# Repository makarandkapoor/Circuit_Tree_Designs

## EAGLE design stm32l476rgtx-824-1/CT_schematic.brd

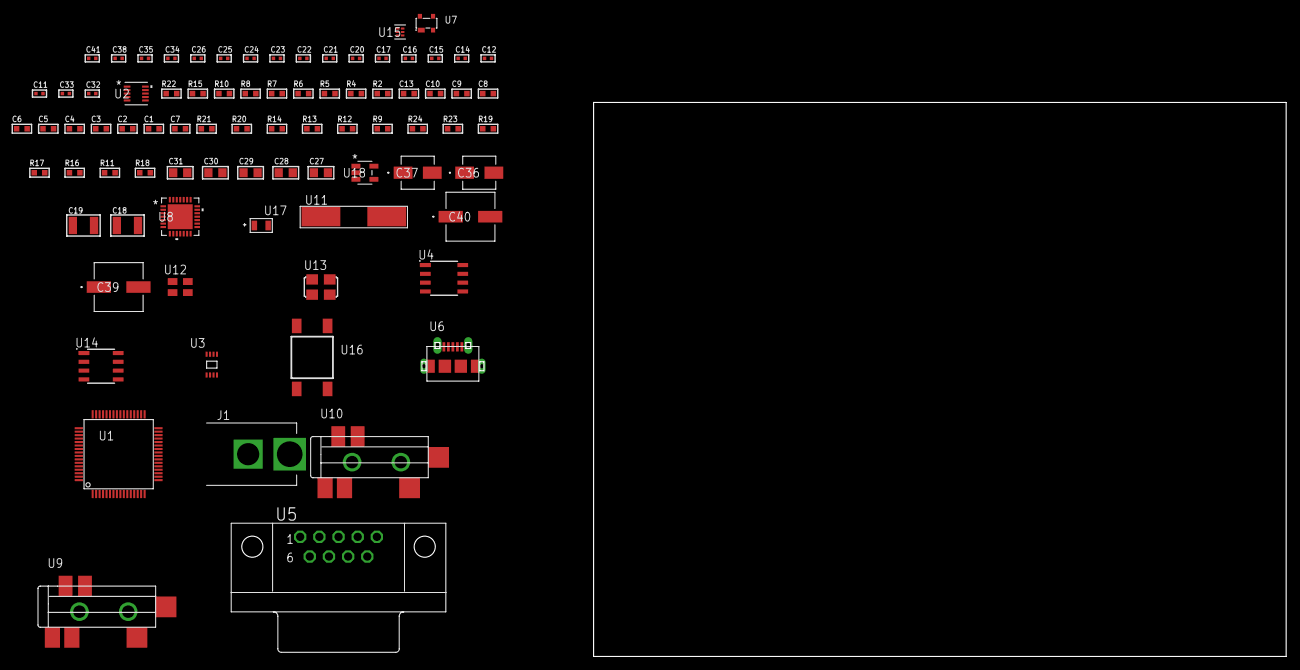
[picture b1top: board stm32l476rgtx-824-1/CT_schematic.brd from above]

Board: 2 copper layers, 124.8 x 80.0 mm, 82 parts (0 on the bottom side), 40 nets, no tracks yet.

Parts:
C1, C10, C13: 1e-06; C0603
C2, C3, C4, C5, C6, C8: 1e-07; C0603
C7: 4.7e-06; C0603
C9: 1e-08; C0603
C11, C12, C14, C15, C17, C22, C23, C24, C25, C26, C38: 1e-07; C0402
C16, C34, C35, C41: 1e-08; C0402
C18, C19: 2.2e-05; C1210
C20, C21: 1e-09; C0402
C27, C28, C29, C30, C31: 1e-05; C0805
C32, C33: 2.2e-11; C0402
C36: 1e-06; EXV-9B
C37: 2.2e-06; EXV-9B
C39, C40: 0.0001; EXV-9H
J1: PJ-037B; PJ-037B_PACKAGE
R2: 1000.0; R0603
R4: 4700.0; R0603
R5, R6, R7, R8: 2200.0; R0603
R9, R20, R21: 10000.0; R0603
R10: 120.0; R0603
R11: 470000.0; R0603
R12, R13, R14: 47000.0; R0603
R15: 680.0; R0603
R16, R17, R19: 100000.0; R0603
R18: 164658.62; R0603
R22: 9100.0; R0603
R23: 680000.0; R0603
R24: 120000.0; R0603
U1: STM32L476RGT6; LQFP64
U2: MAG3110FCR1; DFN-10
U3: 24AA02T-I/MNY; TDFN-8/6MM
U4: SN65HVD230D; SOIC-8
U5: 182-009-113R531; 182-009-MALE
U6: 47590-0001; MICRO_USB_AB
U7: prtr5v0u2ax; SOT143B
U8: WM8731CLSEFL; QFN-28
U9, U10: SJ-43515TS-SMT-TR
U11: ABLS-12.288MHZ-B4-T
U12: ASEK-32.768KHz-ECST; ASEK
U13: ASFL1-25MHZ-NCS; ASFL1
U14: LP2954AIMX/NOPB; LP2954
U15: TPS3895ADRYR; SON-6
U16: 4-1437565-2; SW_4-1437565-2
U17: Q65110A2395; LGM67K-G1J2-24-Z
U18: nc7sz125m5x; NC7SZ125M5X

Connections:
CLK_CRYSTAL_U8_1: C32.1, U8.1, U11.1
CLK_CRYSTAL_U8_2: C33.1, U8.2, U11.2
CLK_U1_3: U1.3, U12.3
CLK_U1_5: U1.5, U13.3
GND: C1.2, C2.2, C3.2, C4.2, C5.2, C6.2, C7.2, C8.2, C9.2, C10.2, C11.2, C12.2, C13.2, C14.2, C15.2, C16.2, C17.2, C21.2, C22.2, C23.2, C24.2, C25.2, C26.2, C27.2, C28.2, C29.2, C30.2, C31.2, C32.2, C33.2, C34.2, C35.2, C36.2, C37.2, C38.2, C39.2, C40.2, C41.2, J1.2, R2.2, R9.2, R11.2, R12.2, R13.2, R14.2, R19.2, R22.2, R24.2, U1.12, U1.18, U1.31, U1.47, U1.63, U2.5, U2.10, U3.4, U3.7, U4.2, U5.5, U6.5, U6.6, U6.7, U6.8, U6.9, U7.1, U8.4, U8.15, U8.19, U8.25, U8.26, U8.29, U9.1, U10.1, U12.2, U13.2, U14.4, U15.2, U17.C, U18.1, U18.3
NET_U1_7: R4.1, U1.7, U18.4
NET_U1_29: R7.1, U1.29, U3.6
NET_U1_30: R8.1, U1.30, U3.5
NET_U1_56: U16.3, U16.4
NET_U1_58: R5.1, U1.58, U2.7
NET_U1_59: R6.1, U1.59, U2.6
NET_U1_60: R9.1, U1.60
NET_U2_1: C11.1, U2.1
NET_U2_4: C14.1, U2.4
NET_U4_6: R10.2, U4.6
NET_U4_8: R11.1, U4.8
NET_U5_2: R10.2, U4.6, U5.2
NET_U5_3: R10.1, U4.7, U5.3
NET_U8_20: C26.1, C31.1, U8.20
NET_U9_2: C19.1, R13.1, U9.2
NET_U9_5: C18.1, R12.1, U9.5
NET_U10_5: C20.1, C21.1, R14.1, R15.1, U10.5
NET_U14_3: R17.1, U14.3
NET_U14_5: R16.1, U14.5
NET_U14_7: R18.2, R19.1, U14.7
NET_U15_1: R21.1, R22.1, U15.1
NET_U15_3: R23.2, R24.1, U15.3
NET_U15_4: R20.1, U15.4, U18.2
NET_U16_1: R2.1, U16.1, U16.2
PROC_CAN1_RX: U1.61, U4.4
PROC_CAN1_TX: U1.62, U4.1
PROC_SAI1_FS_B: U1.20, U8.9, U8.11
PROC_SAI1_SCK_B: U1.55, U8.7
PROC_SAI1_SD_B: U1.57, U8.8
PROC_USB_OTG_FS_DM: U1.44, U6.2, U7.3
PROC_USB_OTG_FS_DP: U1.45, U6.3, U7.2
PROC_USB_OTG_FS_ID: U1.43, U6.4
PROC_USB_OTG_FS_VBUS: U1.42, U6.1, U7.4
VCC_S1_8V1: C36.1, C39.1, C40.1, J1.1, R17.2, U14.8
VCC_TIER1_3V3: C1.1, C2.1, C3.1, C4.1, C5.1, C6.1, C7.1, C8.1, C9.1, C10.1, C12.1, C13.1, C15.1, C16.1, C17.1, C22.1, C23.1, C24.1, C25.1, C27.1, C28.1, C29.1, C30.1, C34.1, C35.1, C37.1, C38.1, C41.1, R4.2, R5.2, R6.2, R7.2, R8.2, R16.2, R18.1, R20.2, R21.2, R23.1, U1.1, U1.13, U1.19, U1.32, U1.48, U1.64, U2.2, U2.8, U3.8, U4.3, U8.3, U8.5, U8.12, U8.18, U12.4, U13.4, U14.1, U15.6, U18.5

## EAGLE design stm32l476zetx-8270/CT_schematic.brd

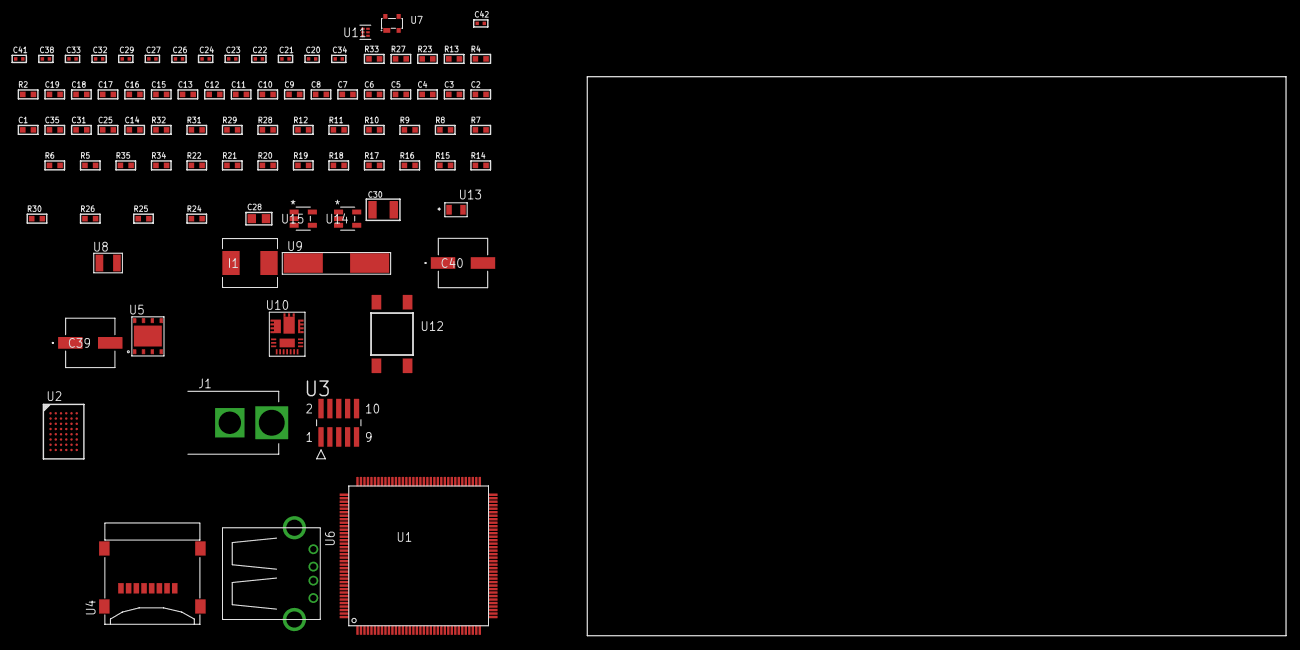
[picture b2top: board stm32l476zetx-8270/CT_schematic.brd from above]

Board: 2 copper layers, 100.0 x 80.0 mm, 90 parts (0 on the bottom side), 83 nets, no tracks yet.

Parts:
C1, C19: 1e-06; C0603
C2, C3, C4, C5, C6, C7, C8, C9, C10, C11, C12, C13, C15, C16, C17: 1e-07; C0603
C14: 4.7e-06; C0603
C18: 1e-08; C0603
C20, C21, C22, C23: 1e-11; C0402
C24, C26, C27, C29, C32, C33, C38: 1e-07; C0402
C25, C31: 2.2e-06; C0603
C28: 1e-05; C0805
C30: 0.0001; C1210
C34: 8.2e-09; C0402
C35: 2.7e-07; C0603
C39, C40: 0.0001; EXV-9H
C41, C42: 1e-08; C0402
I1: 6.8e-07; IND25X25CZ
J1: PJ-037B; PJ-037B_PACKAGE
R2: 1000.0; R0603
R4: 4700.0; R0603
R5, R6, R7, R8, R9, R10, R11, R12, R31, R32: 10000.0; R0603
R13: 5.0; R0603
R14, R15, R16, R17, R18, R19, R20, R21, R22: 100000.0; R0603
R23: 0.1; R0603
R24: 4030.2416170974; R0603
R25: 719.68600305311; R0603
R26: 64.583209876543; R0603
R27: 130.0; R0603
R28: 39000.0; R0603
R29: 49900.0; R0603
R30: 5359.1232876712; R0603
R33: 9100.0; R0603
R34: 680000.0; R0603
R35: 120000.0; R0603
U1: STM32L476ZET6; LQFP144
U2: CY62147GE30-45BVXI; VFBGA48
U3: FTSH-105-01-L-DV-K; SAMTEC_FTSH-105-01-L-DV-K
U4: 0472192001; MOLEX_47219-2001
U5: SST26VF016B-104I/MF; WFDN-8
U6: 61400416021; USB-A-H
U7: prtr5v0u2ax; SOT143B
U8: ABS07-32.768KHZ-7-T
U9: ABLS-25.000MHZ-B2F-T
U10: IR3899MTR1PBF
U11: TPS3895ADRYR; SON-6
U12: 4-1437565-2; SW_4-1437565-2
U13: Q65110A2395; LGM67K-G1J2-24-Z
U14, U15: nc7sz125m5x; NC7SZ125M5X

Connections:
CLK_CRYSTAL_U1_8: C20.1, U1.8, U8.1
CLK_CRYSTAL_U1_9: C21.1, U1.9, U8.2
CLK_CRYSTAL_U1_23: C22.1, U1.23, U9.1
CLK_CRYSTAL_U1_24: C23.1, U1.24, U9.2
GND: C1.2, C2.2, C3.2, C4.2, C5.2, C6.2, C7.2, C8.2, C9.2, C10.2, C11.2, C12.2, C13.2, C14.2, C15.2, C16.2, C17.2, C18.2, C19.2, C20.2, C21.2, C22.2, C23.2, C24.2, C25.2, C26.2, C27.2, C28.2, C29.2, C31.2, C32.2, C33.2, C38.2, C39.2, C40.2, C41.2, C42.2, J1.2, R2.2, R5.2, R12.2, R13.2, R23.1, R23.2, R25.2, R28.2, R30.2, R33.2, R35.2, U1.16, U1.30, U1.31, U1.38, U1.51, U1.61, U1.71, U1.83, U1.94, U1.107, U1.120, U1.130, U1.143, U2.D1, U2.E6, U3.3, U3.5, U4.6, U4.G1, U4.G2, U4.G3, U4.G4, U5.4, U5.9, U6.4, U6.5, U6.6, U7.1, U10.4, U10.11, U10.17, U11.2, U13.C, U14.2, U14.3, U15.1, U15.3
NET_U1_25: R4.1, U1.25, U15.4
NET_U1_138: R5.1, U1.138
NET_U1_142: U12.3, U12.4
NET_U3_9: R13.1, U3.9
NET_U10_1: C34.1, R24.1, R25.1, R26.1, R27.1, U10.1, U10.8
NET_U10_2: C33.1, U10.2
NET_U10_3: C34.2, C35.1, C35.2, U10.3
NET_U10_5: R28.1, U10.5
NET_U10_10: C31.1, U10.10
NET_U10_12: C30.1, I1.1, U10.12
NET_U10_14: C30.2, U10.14
NET_U10_15: R29.1, R30.1, U10.15
NET_U10_ATNET_3: I1.2, R24.2
NET_U10_ATNET_4: C35.2, R26.2
NET_U11_1: R32.1, R33.1, U11.1
NET_U11_3: R34.2, R35.1, U11.3
NET_U11_4: R31.1, U11.4, U14.4, U15.2
NET_U12_1: R2.1, U12.1, U12.2
PROC_FMC_A0: U1.10, U2.A3
PROC_FMC_A1: U1.11, U2.A4
PROC_FMC_A2: U1.12, U2.A5
PROC_FMC_A3: U1.13, U2.B3
PROC_FMC_A4: U1.14, U2.B4
PROC_FMC_A5: U1.15, U2.C3
PROC_FMC_A6: U1.50, U2.C4
PROC_FMC_A7: U1.53, U2.D4
PROC_FMC_A8: U1.54, U2.H2
PROC_FMC_A9: U1.55, U2.H3
PROC_FMC_A10: U1.56, U2.H4
PROC_FMC_A11: U1.57, U2.H5
PROC_FMC_A12: U1.87, U2.G3
PROC_FMC_A13: U1.88, U2.G4
PROC_FMC_A14: U1.89, U2.F3
PROC_FMC_A15: U1.90, U2.F4
PROC_FMC_A16: U1.80, U2.E4
PROC_FMC_A17: U1.81, U2.D3
PROC_FMC_D0: U1.85, U2.B6
PROC_FMC_D1: U1.86, U2.C5
PROC_FMC_D2: U1.114, U2.C6
PROC_FMC_D3: U1.115, U2.D5
PROC_FMC_D4: U1.58, U2.E5
PROC_FMC_D5: U1.59, U2.F5
PROC_FMC_D6: U1.60, U2.F6
PROC_FMC_D7: U1.63, U2.G6
PROC_FMC_D8: U1.64, U2.B1
PROC_FMC_D9: U1.65, U2.C1
PROC_FMC_D10: U1.66, U2.C2
PROC_FMC_D11: U1.67, U2.D2
PROC_FMC_D12: U1.68, U2.E2
PROC_FMC_D13: U1.77, U2.F2
PROC_FMC_D14: U1.78, U2.F1
PROC_FMC_D15: U1.79, U2.G1
PROC_FMC_NBL0: U1.141, U2.A1
PROC_FMC_NE2: R7.1, U1.124, U2.B5
PROC_FMC_NOE: R6.1, U1.118, U2.A2
PROC_FMC_NWE: R8.1, U1.119, U2.G5
PROC_QUADSPI_BK1_IO0: U1.47, U5.5
PROC_QUADSPI_BK1_IO1: U1.46, U5.2
PROC_QUADSPI_BK1_IO2: R21.1, U1.43, U5.3
PROC_QUADSPI_BK1_IO3: R22.1, U1.42, U5.7
PROC_QUADSPI_CLK: U1.69, U5.6
PROC_QUADSPI_NCS: R20.1, U1.70, U5.1
PROC_SDMMC1_CK: R15.1, U1.113, U4.5
PROC_SDMMC1_CMD: R14.1, U1.116, U4.3
PROC_SDMMC1_D0: R16.1, U1.98, U4.7
PROC_SDMMC1_D1: R17.1, U1.99, U4.8
PROC_SDMMC1_D2: R18.1, U1.111, U4.1
PROC_SDMMC1_D3: R19.1, U1.112, U4.2
PROC_SYS_JTCK_SWCLK: R12.1, U1.109, U3.4
PROC_SYS_JTDI: R10.1, U1.110, U3.8
PROC_SYS_JTDO_SWO: U1.133, U3.6
PROC_SYS_JTMS_SWDIO: R11.1, U1.105, U3.2
PROC_USB_OTG_FS_DM: U1.103, U6.2, U7.3
PROC_USB_OTG_FS_DP: U1.104, U6.3, U7.2
PROC_USB_OTG_FS_VBUS: U1.101, U6.1, U7.4
RST_OUT_U3_JTAG_RST_B: R9.1, U3.10, U14.1
VCC_S1_16V2: C32.1, C39.1, C40.1, J1.1, R29.2, U10.9
VCC_TIER1_3V3: C1.1, C2.1, C3.1, C4.1, C5.1, C6.1, C7.1, C8.1, C9.1, C10.1, C11.1, C12.1, C13.1, C14.1, C15.1, C16.1, C17.1, C18.1, C19.1, C24.1, C25.1, C26.1, C27.1, C28.1, C29.1, C38.1, C41.1, C42.1, I1.2, R4.2, R6.2, R7.2, R8.2, R9.2, R10.2, R11.2, R14.2, R15.2, R16.2, R17.2, R18.2, R19.2, R20.2, R21.2, R22.2, R24.2, R31.2, R32.2, R34.1, U1.6, U1.17, U1.32, U1.33, U1.39, U1.52, U1.62, U1.72, U1.84, U1.95, U1.106, U1.108, U1.121, U1.131, U1.144, U2.D6, U2.E1, U3.1, U4.4, U5.8, U11.6, U14.5, U15.5

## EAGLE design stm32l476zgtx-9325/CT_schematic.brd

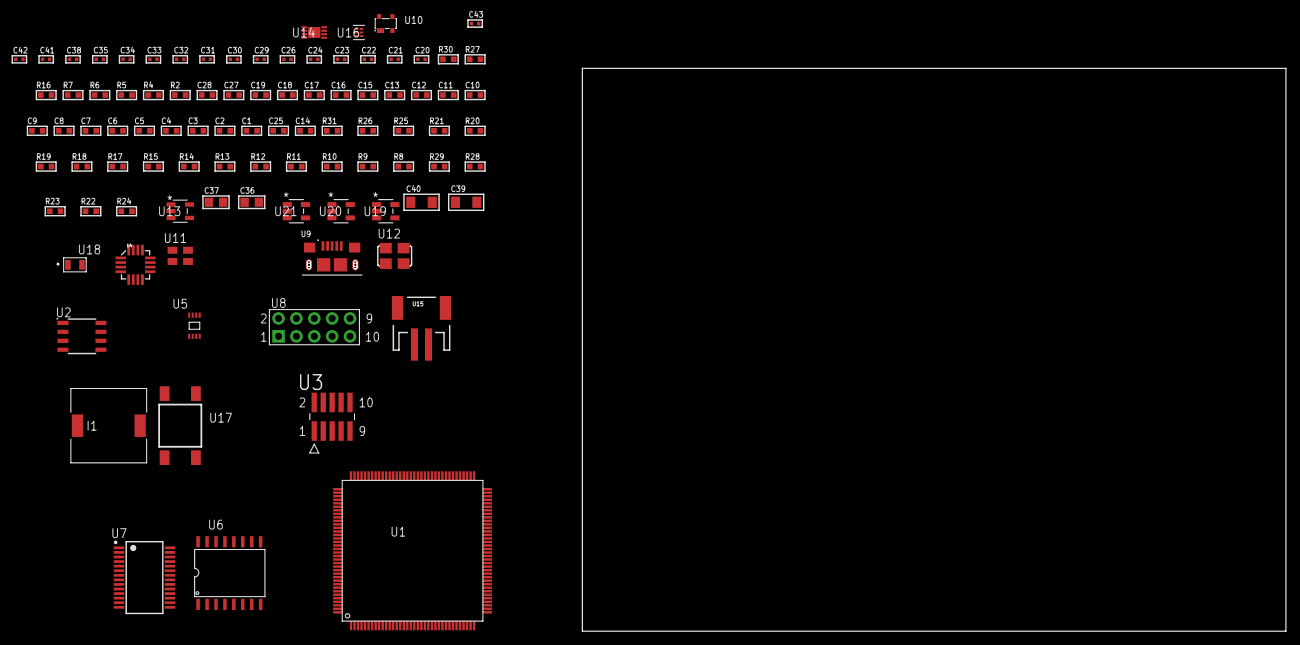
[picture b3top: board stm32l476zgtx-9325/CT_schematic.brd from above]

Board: 2 copper layers, 94 parts (0 on the bottom side), 61 nets, no tracks yet.

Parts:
C1, C19, C27, C28: 1e-06; C0603
C2, C3, C4, C5, C6, C7, C8, C9, C10, C11, C12, C13, C15, C16, C17: 1e-07; C0603
C14: 4.7e-06; C0603
C18: 1e-08; C0603
C20, C22, C23, C24, C26, C34, C35, C41, C42, C43: 1e-08; C0402
C21, C29, C30, C31, C32, C33, C38: 1e-07; C0402
C25: 4.7e-07; C0603
C36, C37: 1e-05; C0805
C39, C40: 1e-05; C1206
I1: 2.5e-06; DR1040
R2: 1000.0; R0603
R4, R5: 4700.0; R0603
R6, R7: 2200.0; R0603
R8, R9, R10, R11, R12, R13, R14, R15, R17, R18, R19, R20, R21, R25, R26, R31: 10000.0; R0603
R16: 5.0; R0603
R22: 100000.0; R0603
R23: 220000.0; R0603
R24: 1000000.0; R0603
R27: 9100.0; R0603
R28: 680000.0; R0603
R29: 120000.0; R0603
R30: 2000.0; R0603
U1: STM32L476ZGT6; LQFP144
U2: AT25020B-SSHL-T; SOIC-8
U3: FTSH-105-01-L-DV-K; SAMTEC_FTSH-105-01-L-DV-K
U4: l3g4200d; LGA-16
U5: 24AA16-I/MC; TDFN-8/6MM
U6: S25FL128SDSMFI000
U7: ST3241EBPR; SSOP-28
U8: HTSS-105-01-G-D
U9: 10118193-0001LF; FCI_10118193-0001LF
U10: prtr5v0u2ax; SOT143B
U11: ASEK-32.768KHz-ECST; ASEK
U12: ASFL1-25MHZ-NCS; ASFL1
U13: ltc3406es5; TSOT-23-5
U14: MCP73831T-2ACI/MC; DFN8_2X3MC
U15: S2B-PH-SM4-TB(LF)(SN); JST-2-SMD
U16: TPS3895ADRYR; SON-6
U17: 4-1437565-2; SW_4-1437565-2
U18: Q65110A2395; LGM67K-G1J2-24-Z
U19, U20, U21: nc7sz125m5x; NC7SZ125M5X

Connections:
CLK_U1_8: U1.8, U11.3
CLK_U1_23: U1.23, U12.3
GND: C1.2, C2.2, C3.2, C4.2, C5.2, C6.2, C7.2, C8.2, C9.2, C10.2, C11.2, C12.2, C13.2, C14.2, C15.2, C16.2, C17.2, C18.2, C19.2, C20.2, C21.2, C22.2, C23.2, C24.2, C26.2, C27.2, C28.2, C29.2, C32.2, C33.2, C34.2, C35.2, C36.2, C37.1, C37.2, C38.2, C39.2, C40.2, C41.2, C42.2, C43.2, R2.2, R8.2, R15.2, R16.2, R17.1, R17.2, R23.2, R27.2, R29.2, R30.2, U1.16, U1.30, U1.31, U1.38, U1.51, U1.61, U1.71, U1.83, U1.94, U1.107, U1.120, U1.130, U1.143, U2.4, U3.3, U3.5, U4.8, U4.9, U4.10, U4.11, U4.12, U4.13, U5.4, U5.7, U6.10, U7.23, U7.25, U8.9, U9.5, U9.6, U9.7, U9.8, U9.9, U10.1, U11.2, U12.2, U13.2, U14.6, U14.9, U15.2, U16.2, U18.C, U19.2, U19.3, U20.1, U20.3, U21.1, U21.3
INPUT_USBPOWER_5V: C39.1, R31.2, U9.1, U10.4, U14.1, U14.2
NET_U1_25: R5.1, U1.25, U21.4
NET_U1_128: R7.1, U1.128, U5.5
NET_U1_129: R6.1, U1.129, U5.6
NET_U1_138: R8.1, U1.138
NET_U1_142: U17.3, U17.4
NET_U2_3: R9.1, U2.3
NET_U2_7: R11.1, U2.7
NET_U3_9: R16.1, U3.9
NET_U4_14: C24.1, C25.1, U4.14
NET_U6_3: R4.1, U6.3, U20.4
NET_U7_1: C31.1, U7.1
NET_U7_2: C31.2, U7.2
NET_U7_3: C33.1, U7.3
NET_U7_22: R22.1, U7.22
NET_U7_24: C30.2, U7.24
NET_U7_27: C32.1, U7.27
NET_U7_28: C30.1, U7.28
NET_U8_3: U7.4, U8.3
NET_U8_4: U7.5, U8.4
NET_U8_5: U7.9, U8.5
NET_U8_6: U7.10, U8.6
NET_U13_3: I1.1, U13.3
NET_U13_5: R23.1, R24.1, U13.5
NET_U13_ATNET_3: I1.2, R24.2
NET_U14_5: R31.1, U14.5
NET_U14_8: R30.1, U14.8
NET_U16_1: R26.1, R27.1, U16.1
NET_U16_3: R28.2, R29.1, U16.3
NET_U16_4: R25.1, U16.4, U19.4, U20.2, U21.2
NET_U17_1: R2.1, U17.1, U17.2
PROC_LPUART1_CTS: U1.74, U7.13
PROC_LPUART1_RTS: U1.73, U7.18
PROC_LPUART1_RX: U1.26, U7.19
PROC_LPUART1_TX: U1.27, U7.14
PROC_QUADSPI_BK1_IO0: U1.47, U6.15
PROC_QUADSPI_BK1_IO1: U1.46, U6.8
PROC_QUADSPI_BK1_IO2: R20.1, U1.43, U6.9
PROC_QUADSPI_BK1_IO3: R21.1, U1.42, U6.1
PROC_QUADSPI_CLK: U1.63, U6.16
PROC_QUADSPI_NCS: R19.1, U1.64, U6.7
PROC_SPI1_MISO: U1.67, U4.4
PROC_SPI1_MOSI: U1.68, U4.3
PROC_SPI1_NSS: R18.1, U1.40, U4.5
PROC_SPI1_SCK: U1.41, U4.2
PROC_SPI2_MISO: U1.28, U2.2
PROC_SPI2_MOSI: U1.29, U2.5
PROC_SPI2_NSS: R10.1, U1.114, U2.1
PROC_SPI2_SCK: U1.69, U2.6
PROC_SYS_JTCK_SWCLK: R15.1, U1.109, U3.4
PROC_SYS_JTDI: R13.1, U1.110, U3.8
PROC_SYS_JTDO_SWO: U1.133, U3.6
PROC_SYS_JTMS_SWDIO: R14.1, U1.105, U3.2
PROC_USB_OTG_FS_DM: U9.2, U10.3
PROC_USB_OTG_FS_DP: U9.3, U10.2
RST_OUT_U3_JTAG_RST_B: R12.1, U3.10, U19.1
VCC_S1_3V7: C36.1, C40.1, U13.4, U14.3, U14.4, U15.1
VCC_TIER1_3V3: C1.1, C2.1, C3.1, C4.1, C5.1, C6.1, C7.1, C8.1, C9.1, C10.1, C11.1, C12.1, C13.1, C14.1, C15.1, C16.1, C17.1, C18.1, C19.1, C20.1, C21.1, C22.1, C23.1, C26.1, C27.1, C28.1, C29.1, C34.1, C35.1, C37.2, C38.1, C41.1, C42.1, C43.1, I1.2, R4.2, R5.2, R6.2, R7.2, R9.2, R10.2, R11.2, R12.2, R13.2, R14.2, R18.2, R19.2, R20.2, R21.2, R22.2, R24.2, R25.2, R26.2, R28.1, U1.6, U1.17, U1.32, U1.33, U1.39, U1.52, U1.62, U1.72, U1.84, U1.95, U1.106, U1.108, U1.121, U1.131, U1.144, U2.8, U3.1, U4.1, U4.15, U4.16, U5.8, U6.2, U6.14, U7.26, U11.4, U12.4, U16.6, U19.5, U20.5, U21.5

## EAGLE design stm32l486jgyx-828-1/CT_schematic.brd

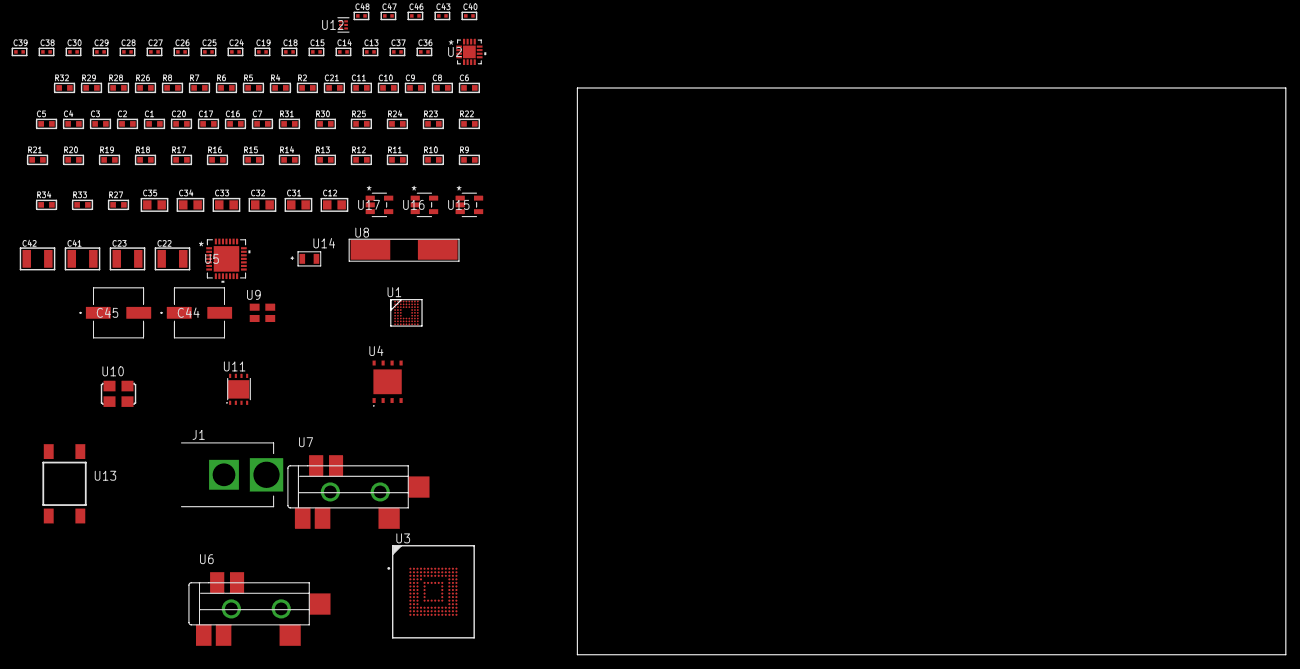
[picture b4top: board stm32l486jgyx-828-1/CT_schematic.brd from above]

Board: 2 copper layers, 126.3 x 80.0 mm, 98 parts (0 on the bottom side), 47 nets, no tracks yet.

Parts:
C1, C11, C21: 1e-06; C0603
C2, C3, C4, C5, C6, C8, C9: 1e-07; C0603
C7: 4.7e-06; C0603
C10: 1e-08; C0603
C12: 4.7e-06; C0805
C13, C14, C15, C18, C19, C26, C27, C28, C29, C30, C43: 1e-07; C0402
C16, C17, C20: 2.2e-06; C0603
C22, C23: 2.2e-05; C1210
C24, C25: 1e-09; C0402
C31, C32, C33, C34, C35: 1e-05; C0805
C36, C37: 2.2e-11; C0402
C38, C39, C40, C46, C47, C48: 1e-08; C0402
C41, C42: 1e-05; C1210
C44, C45: 0.0001; EXV-9H
J1: PJ-037B; PJ-037B_PACKAGE
R2, R29: 1000.0; R0603
R4, R5, R6: 4700.0; R0603
R7, R8: 2200.0; R0603
R9, R10, R21, R22, R30, R31: 10000.0; R0603
R11, R12, R13, R14, R15, R16, R17, R18, R19, R20: 34000.0; R0603
R23, R24, R25: 47000.0; R0603
R26: 680.0; R0603
R27: 100000.0; R0603
R28: 2231.0; R0603
R32: 9100.0; R0603
R33: 680000.0; R0603
R34: 120000.0; R0603
U1: STM32L486JGY6; WLCSP72
U2: MMA8451QT; QFN-16
U3: mtfc4gmcdm; TFBGA-153
U4: MX25R6435FZAIH0; WSON-8-PAD
U5: WM8731CLSEFL; QFN-28
U6, U7: SJ-43515TS-SMT-TR
U8: ABLS-12.288MHZ-B4-T
U9: ASEK-32.768KHz-ECST; ASEK
U10: ASFL1-25MHZ-NCS; ASFL1
U11: LP3878SDX-ADJ/NOPB; WSON-8
U12: TPS3895ADRYR; SON-6
U13: 4-1437565-2; SW_4-1437565-2
U14: Q65110A2395; LGM67K-G1J2-24-Z
U15, U16, U17: nc7sz125m5x; NC7SZ125M5X

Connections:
CLK_CRYSTAL_U5_1: C36.1, U5.1, U8.1
CLK_CRYSTAL_U5_2: C37.1, U5.2, U8.2
CLK_U1_C9: U1.C9, U9.3
CLK_U1_D9: U1.D9, U10.3
GND: C1.2, C2.2, C3.2, C4.2, C5.2, C6.2, C7.2, C8.2, C9.2, C10.2, C11.2, C12.2, C13.2, C14.2, C15.2, C16.2, C17.2, C18.2, C19.2, C20.2, C21.2, C25.2, C26.2, C27.2, C28.2, C29.2, C30.2, C31.2, C32.2, C33.2, C34.2, C35.2, C36.2, C37.2, C38.2, C39.2, C40.2, C41.2, C42.2, C43.2, C44.2, C45.2, C46.2, C47.2, C48.2, J1.2, R2.2, R9.2, R23.2, R24.2, R25.2, R29.2, R32.2, R34.2, U1.A8, U1.B1, U1.G9, U1.J2, U1.J9, U2.5, U2.10, U2.12, U2.17, U3.C4, U3.E7, U3.G5, U3.H10, U3.K8, U3.N2, U3.N5, U3.P4, U3.P6, U4.4, U4.PAD, U5.4, U5.15, U5.19, U5.25, U5.26, U5.29, U6.1, U7.1, U9.2, U10.2, U11.3, U11.PAD, U12.2, U14.C, U15.1, U15.3, U16.1, U16.3, U17.1, U17.3
NET_U1_A5: R7.1, U1.A5, U2.4
NET_U1_A7: R8.1, U1.A7, U2.6
NET_U1_D7: R9.1, U1.D7
NET_U1_E9: R6.1, U1.E9, U17.4
NET_U1_H9: C10.1, C11.1, U1.G8, U1.H9
NET_U1_J7: U13.3, U13.4
NET_U2_2: C14.1, U2.2
NET_U2_7: R10.1, U2.7
NET_U3_C2: C17.1, C18.1, U3.C2
NET_U3_K5: R4.1, U3.K5, U15.4
NET_U4_7: R5.1, U1.H5, U4.7, U16.4
NET_U5_20: C30.1, C35.1, U5.20
NET_U6_2: C23.1, R24.1, U6.2
NET_U6_5: C22.1, R23.1, U6.5
NET_U7_5: C24.1, C25.1, R25.1, R26.1, U7.5
NET_U11_1: C40.1, U11.1
NET_U11_6: R28.2, R29.1, U11.6
NET_U11_8: R27.1, U11.8
NET_U12_1: R31.1, R32.1, U12.1
NET_U12_3: R33.2, R34.1, U12.3
NET_U12_4: R30.1, U12.4, U15.2, U16.2, U17.2
NET_U13_1: R2.1, U13.1, U13.2
PROC_QUADSPI_BK1_IO0: U1.J4, U4.5
PROC_QUADSPI_BK1_IO1: U1.J5, U4.2
PROC_QUADSPI_BK1_IO2: R22.1, U1.H4, U4.3
PROC_QUADSPI_CLK: U1.H3, U4.6
PROC_QUADSPI_NCS: R21.1, U1.G3, U4.1
PROC_SAI1_FS_B: U1.B7, U5.9, U5.11
PROC_SAI1_SCK_B: U1.A6, U5.7
PROC_SAI1_SD_B: U1.C7, U5.8
PROC_SDMMC1_CK: R20.1, U1.B3, U3.M6
PROC_SDMMC1_CMD: R19.1, U1.A3, U3.M5
PROC_SDMMC1_D0: R11.1, U1.F2, U3.A3
PROC_SDMMC1_D1: R12.1, U1.E1, U3.A4
PROC_SDMMC1_D2: R13.1, U1.D3, U3.A5
PROC_SDMMC1_D3: R14.1, U1.C3, U3.B2
PROC_SDMMC1_D4: R15.1, U1.E7, U3.B3
PROC_SDMMC1_D5: R16.1, U1.E8, U3.B4
PROC_SDMMC1_D6: R17.1, U1.F3, U3.B5
PROC_SDMMC1_D7: R18.1, U1.F1, U3.B6
VCC_S1_11V4: C41.1, C44.1, C45.1, J1.1, R27.2, U11.4
VCC_TIER1_3V3: C1.1, C2.1, C3.1, C4.1, C5.1, C6.1, C7.1, C8.1, C9.1, C12.1, C13.1, C15.1, C16.1, C19.1, C20.1, C21.1, C26.1, C27.1, C28.1, C29.1, C31.1, C32.1, C33.1, C34.1, C38.1, C39.1, C42.1, C43.1, C46.1, C47.1, C48.1, R4.2, R5.2, R6.2, R7.2, R8.2, R10.2, R11.2, R12.2, R13.2, R14.2, R15.2, R16.2, R17.2, R18.2, R19.2, R20.2, R21.2, R22.2, R28.1, R30.2, R31.2, R33.1, U1.A1, U1.A9, U1.B6, U1.B9, U1.J1, U1.J8, U2.1, U2.14, U3.C6, U3.E6, U3.F5, U3.J10, U3.K9, U3.M4, U3.N4, U3.P3, U3.P5, U4.8, U5.3, U5.5, U5.12, U5.18, U9.4, U10.4, U11.5, U12.6, U15.5, U16.5, U17.5

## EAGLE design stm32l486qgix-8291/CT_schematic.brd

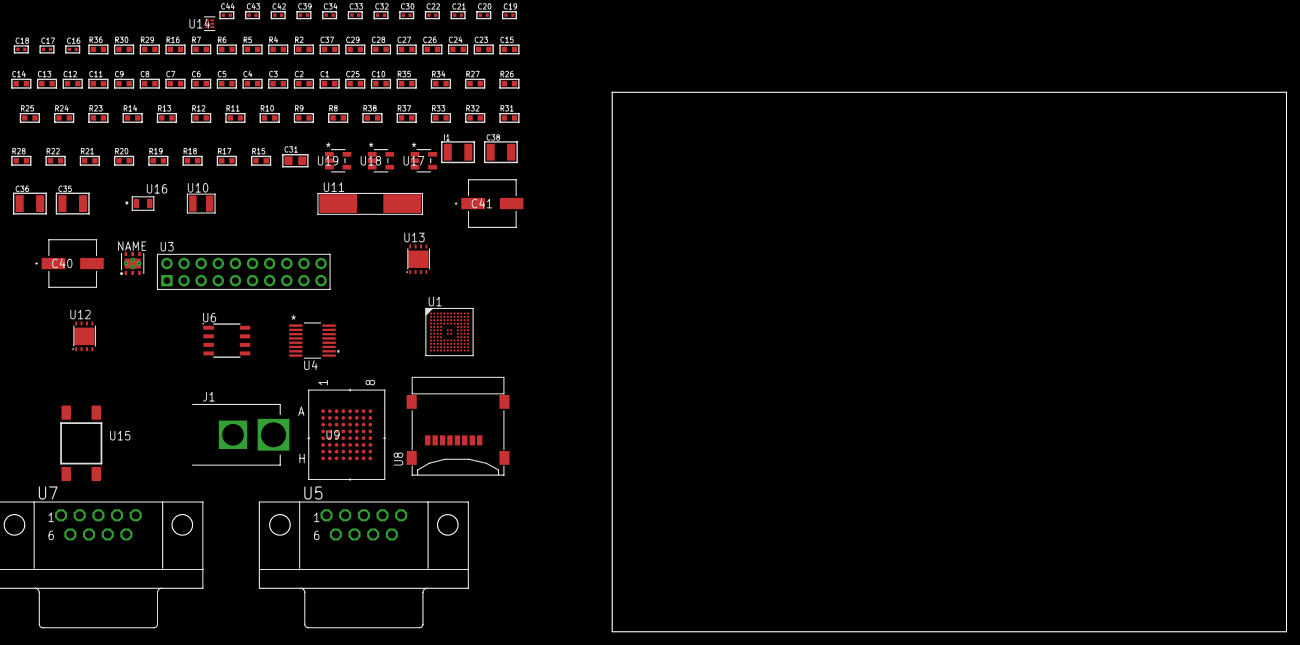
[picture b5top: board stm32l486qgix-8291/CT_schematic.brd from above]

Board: 2 copper layers, 100.0 x 80.0 mm, 101 parts (0 on the bottom side), 101 nets, no tracks yet.

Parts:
C1, C15, C23, C24, C26, C27, C28, C29: 1e-06; C0603
C2, C3, C4, C5, C6, C7, C8, C9, C11, C12, C13: 1e-07; C0603
C10: 4.7e-06; C0603
C14: 1e-08; C0603
C16, C17, C18, C19: 1e-11; C0402
C20, C32, C33, C34, C42, C43, C44: 1e-08; C0402
C21, C22, C30, C39: 1e-07; C0402
C25: 2.2e-07; C0603
C31: 1e-05; C0805
C35, C36, C38: 1e-05; C1210
C37: 8e-07; R0603
C40, C41: 0.0001; EXV-9H
I1: 1e-05; L1210
J1: PJ-037B; PJ-037B_PACKAGE
R2, R30: 1000.0; R0603
R4, R5: 4700.0; R0603
R6, R7: 2200.0; R0603
R8, R9, R10, R11, R12, R13, R14, R23, R24, R25, R26, R27, R34, R35: 10000.0; R0603
R15, R17, R18, R19, R20, R21, R22, R28, R31, R33: 100000.0; R0603
R16: 120.0; R0603
R29: 2231.0; R0603
R32: 300000.0; R0603
R36: 9100.0; R0603
R37: 680000.0; R0603
R38: 120000.0; R0603
U1: STM32L486QGI6; UFBGA132
U2: HDC1080DMBR; WSON-6
U3: TST-110-05-T-D-RA
U4: LTC2804CGN-1#PBF; SSOP-16
U5, U7: 182-009-113R531; 182-009-MALE
U6: MCP2562-E/SN; SOIC-8
U8: 0472192001; MOLEX_47219-2001
U9: mt28ew512aba1HPC-0AAT; LBGA-64
U10: ABS07-32.768KHZ-7-T
U11: ABLS-25.000MHZ-B2F-T
U12: LP3878SDX-ADJ/NOPB; WSON-8
U13: LP2951ACSDX/NOPB; WSON-8
U14: TPS3895ADRYR; SON-6
U15: 4-1437565-2; SW_4-1437565-2
U16: Q65110A2395; LGM67K-G1J2-24-Z
U17, U18, U19: nc7sz125m5x; NC7SZ125M5X

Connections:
CLK_CRYSTAL_U1_D1: C16.1, U1.D1, U10.1
CLK_CRYSTAL_U1_E1: C17.1, U1.E1, U10.2
CLK_CRYSTAL_U1_F1: C18.1, U1.F1, U11.1
CLK_CRYSTAL_U1_G1: C19.1, U1.G1, U11.2
GND: C1.2, C2.2, C3.2, C4.2, C5.2, C6.2, C7.2, C8.2, C9.2, C10.2, C11.2, C12.2, C13.2, C14.2, C15.2, C16.2, C17.2, C18.2, C19.2, C20.2, C21.2, C22.2, C23.2, C24.2, C26.2, C27.2, C28.2, C29.2, C30.2, C31.2, C32.2, C33.2, C34.2, C35.2, C36.2, C37.2, C38.2, C39.2, C40.2, C41.2, C42.2, C43.2, C44.2, J1.2, R2.2, R8.2, R14.2, R30.2, R33.2, R36.2, R38.2, U1.D3, U1.E3, U1.F2, U1.F6, U1.F7, U1.F11, U1.F12, U1.J1, U2.2, U2.PAD, U3.4, U3.6, U3.8, U3.10, U3.12, U3.14, U3.16, U3.18, U3.20, U4.8, U5.5, U6.2, U6.8, U7.5, U8.6, U8.G1, U8.G2, U8.G3, U8.G4, U9.E8, U9.H2, U9.H7, U12.3, U12.PAD, U13.3, U13.4, U13.PAD, U14.2, U16.C, U17.2, U17.3, U18.1, U18.3, U19.1, U19.3
NET_U1_A4: R8.1, U1.A4
NET_U1_B3: R7.1, U1.B3, U2.1
NET_U1_B5: R6.1, U1.B5, U2.6
NET_U1_H2: R5.1, U1.H2, U19.4
NET_U1_M6: U15.3, U15.4
NET_U3_19: R14.1, U3.19
NET_U4_6: C23.1, U4.6
NET_U4_7: C25.1, I1.2, U4.7
NET_U4_9: C24.1, U4.9
NET_U4_10: C25.2, U4.10
NET_U4_11: R15.1, U4.11
NET_U5_2: U4.1, U5.2
NET_U5_3: U4.3, U5.3
NET_U5_7: U4.2, U5.7
NET_U5_8: U4.4, U5.8
NET_U6_6: R16.2, U6.6
NET_U7_2: R16.2, U6.6, U7.2
NET_U7_3: R16.1, U6.7, U7.3
NET_U9_B4: R26.1, U9.B4
NET_U9_B5: R4.1, U9.B5, U18.4
NET_U12_1: C34.1, U12.1
NET_U12_6: R29.2, R30.1, U12.6
NET_U12_8: R28.1, U12.8
NET_U13_5: R31.1, U13.5
NET_U13_7: R32.2, R33.1, U13.7
NET_U14_1: R35.1, R36.1, U14.1
NET_U14_3: R37.2, R38.1, U14.3
NET_U14_4: R34.1, U14.4, U17.4, U18.2, U19.2
NET_U15_1: R2.1, U15.1, U15.2
PROC_CAN1_RX: U1.A3, U6.4
PROC_CAN1_TX: U1.A12, U6.1
PROC_FMC_A0: U1.D6, U9.E2
PROC_FMC_A1: U1.D5, U9.D2
PROC_FMC_A2: U1.D4, U9.C2
PROC_FMC_A3: U1.E4, U9.A2
PROC_FMC_A4: U1.F3, U9.B2
PROC_FMC_A5: U1.F4, U9.D3
PROC_FMC_A6: U1.J7, U9.C3
PROC_FMC_A7: U1.K7, U9.A3
PROC_FMC_A8: U1.J8, U9.B6
PROC_FMC_A9: U1.J9, U9.A6
PROC_FMC_A10: U1.H9, U9.C6
PROC_FMC_A11: U1.G9, U9.D6
PROC_FMC_A12: U1.G10, U9.B7
PROC_FMC_A13: U1.F9, U9.A7
PROC_FMC_A14: U1.F10, U9.C7
PROC_FMC_A15: U1.E9, U9.D7
PROC_FMC_A16: U1.J11, U9.E7
PROC_FMC_A17: U1.J10, U9.B3
PROC_FMC_A18: U1.H12, U9.C4
PROC_FMC_A19: U1.A1, U9.D5
PROC_FMC_A20: U1.B1, U9.D4
PROC_FMC_A21: U1.C2, U9.C5
PROC_FMC_A22: U1.D2, U9.B8
PROC_FMC_A23: U1.B2, U9.C8
PROC_FMC_A24: U1.C7, U9.F8
PROC_FMC_D0: U1.H11, U9.E3
PROC_FMC_D1: U1.H10, U9.H3
PROC_FMC_D2: U1.C9, U9.E4
PROC_FMC_D3: U1.B9, U9.H4
PROC_FMC_D4: U1.M7, U9.H5
PROC_FMC_D5: U1.L7, U9.E5
PROC_FMC_D6: U1.M8, U9.H6
PROC_FMC_D7: U1.L8, U9.E6
PROC_FMC_D8: U1.M9, U9.F3
PROC_FMC_D9: U1.L9, U9.G3
PROC_FMC_D10: U1.M10, U9.F4
PROC_FMC_D11: U1.M11, U9.G4
PROC_FMC_D12: U1.M12, U9.F5
PROC_FMC_D13: U1.K9, U9.G6
PROC_FMC_D14: U1.K8, U9.F6
PROC_FMC_D15: U1.J12, U9.G7
PROC_FMC_NBL0: R27.1, U1.C3, U9.F7
PROC_FMC_NE3: R23.1, U1.D8, U9.F2
PROC_FMC_NOE: R24.1, U1.B7, U9.G2
PROC_FMC_NWAIT: U1.B6, U9.A4
PROC_FMC_NWE: R25.1, U1.A6, U9.A5
PROC_LPUART1_CTS: U1.K12, U4.13
PROC_LPUART1_RTS: U1.G4, U4.15
PROC_LPUART1_RX: U1.H1, U4.16
PROC_LPUART1_TX: U1.H4, U4.14
PROC_SDMMC1_CK: R18.1, U1.B10, U8.5
PROC_SDMMC1_CMD: R17.1, U1.C8, U8.3
PROC_SDMMC1_D0: R19.1, U1.E10, U8.7
PROC_SDMMC1_D1: R20.1, U1.D12, U8.8
PROC_SDMMC1_D2: R21.1, U1.B11, U8.1
PROC_SDMMC1_D3: R22.1, U1.C10, U8.2
PROC_SYS_JTCK_SWCLK: R12.1, U1.A10, U3.9
PROC_SYS_JTDI: R10.1, U1.A9, U3.5
PROC_SYS_JTDO_SWO: U1.A8, U3.13
PROC_SYS_JTMS_SWDIO: R11.1, U1.A11, U3.7
PROC_SYS_JTRST: R9.1, U1.A7, U3.3
RST_OUT_U3_SRESET_B: R13.1, U3.15, U17.1
VCC_S1_13V8: C35.1, C37.1, C40.1, C41.1, J1.1, R28.2, U12.4, U13.8
VCC_TIER1_3V3: C1.1, C2.1, C3.1, C4.1, C5.1, C6.1, C7.1, C8.1, C9.1, C10.1, C11.1, C12.1, C13.1, C14.1, C15.1, C20.1, C21.1, C22.1, C26.1, C27.1, C29.1, C30.1, C31.1, C32.1, C33.1, C36.1, C39.1, C42.1, C43.1, C44.1, I1.1, R4.2, R5.2, R6.2, R7.2, R9.2, R10.2, R11.2, R12.2, R13.2, R15.2, R17.2, R18.2, R19.2, R20.2, R21.2, R22.2, R23.2, R24.2, R25.2, R26.2, R27.2, R29.1, R34.2, R35.2, R37.1, U1.C4, U1.C11, U1.E2, U1.G2, U1.G6, U1.G7, U1.G11, U1.G12, U1.H3, U1.L1, U1.M1, U2.5, U3.1, U3.2, U4.5, U4.12, U6.5, U8.4, U9.D8, U9.F1, U9.G5, U12.5, U14.6, U17.5, U18.5, U19.5
VCC_TIER1_5V0: C28.1, C38.1, R31.2, R32.1, U6.3, U13.1

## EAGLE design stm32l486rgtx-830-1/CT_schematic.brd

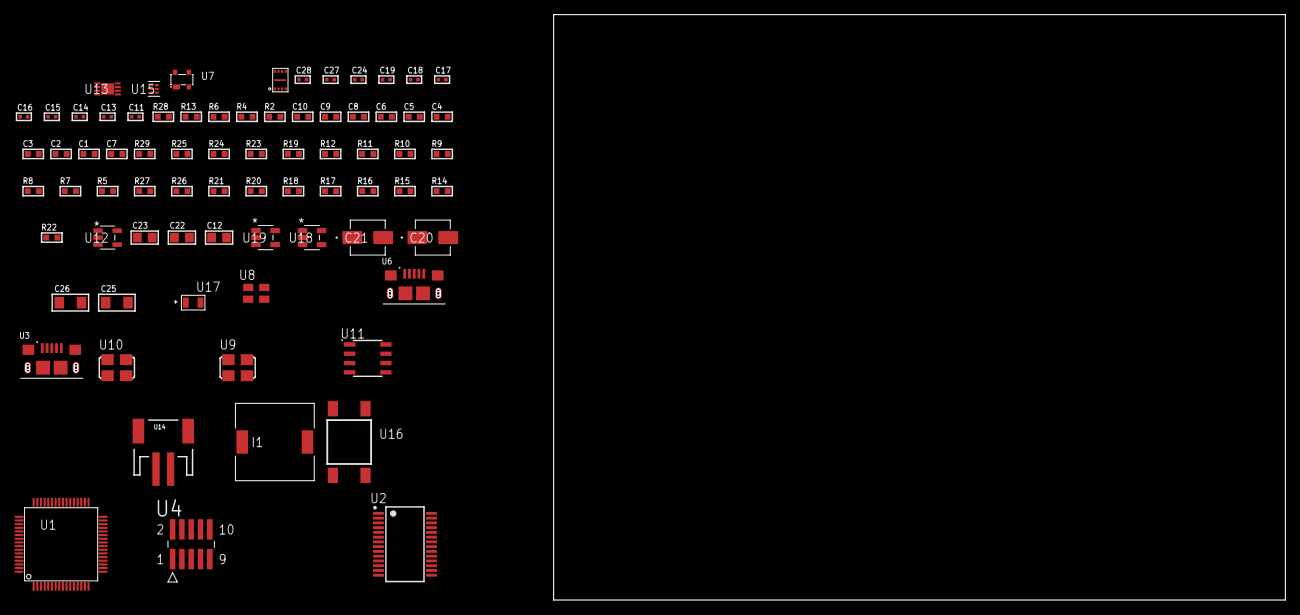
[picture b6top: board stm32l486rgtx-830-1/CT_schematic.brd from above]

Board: 2 copper layers, 172.1 x 80.0 mm, 75 parts (0 on the bottom side), 47 nets, no tracks yet.

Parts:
C1, C10: 1e-06; C0603
C2, C3, C4, C5, C6, C8: 1e-07; C0603
C7: 4.7e-06; C0603
C9: 1e-08; C0603
C11, C13, C14, C15, C16, C24: 1e-07; C0402
C12: 4.7e-06; C0805
C17, C18, C19, C27, C28: 1e-08; C0402
C20: 1e-06; EXV-9B
C21: 2.2e-06; EXV-9B
C22, C23: 1e-05; C0805
C25, C26: 1e-05; C1206
I1: 2.5e-06; DR1040
R2: 1000.0; R0603
R4, R6: 4700.0; R0603
R5, R7, R8, R9, R10, R11, R12, R23, R24, R29: 10000.0; R0603
R13: 5.0; R0603
R14, R15, R16, R17, R18, R20: 100000.0; R0603
R19: 47000.0; R0603
R21: 220000.0; R0603
R22: 1000000.0; R0603
R25: 82000.0; R0603
R26: 300000.0; R0603
R27: 120000.0; R0603
R28: 2000.0; R0603
U1: STM32L486RGT6; LQFP64
U2: FT232RL-REEL; SSOP-28
U3, U6: 10118193-0001LF; FCI_10118193-0001LF
U4: FTSH-105-01-L-DV-K; SAMTEC_FTSH-105-01-L-DV-K
U5: SST26WF040BT-104I/NP; USON-8
U7: prtr5v0u2ax; SOT143B
U8: ASEK-32.768KHz-ECST; ASEK
U9: ASFL1-12MHZ-NCS; ASFL1
U10: ASFL1-25MHZ-NCS; ASFL1
U11: LP2954AIMX/NOPB; LP2954
U12: ltc3406es5; TSOT-23-5
U13: MCP73831T-2ACI/MC; DFN8_2X3MC
U14: S2B-PH-SM4-TB(LF)(SN); JST-2-SMD
U15: TPS3895ADRYR; SON-6
U16: 4-1437565-2; SW_4-1437565-2
U17: Q65110A2395; LGM67K-G1J2-24-Z
U18, U19: nc7sz125m5x; NC7SZ125M5X

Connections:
CLK_U1_3: U1.3, U8.3
CLK_U1_5: U1.5, U10.3
CLK_U2_27: U2.27, U9.3
GND: C1.2, C2.2, C3.2, C4.2, C5.2, C6.2, C7.2, C8.2, C9.2, C10.2, C11.2, C12.2, C13.2, C14.2, C15.2, C16.2, C17.2, C18.2, C19.2, C20.2, C21.2, C22.2, C23.1, C23.2, C24.2, C25.2, C26.2, C27.2, C28.2, R2.2, R5.2, R8.2, R12.2, R13.2, R20.2, R21.2, R25.2, R27.2, R28.2, U1.12, U1.18, U1.31, U1.47, U1.63, U2.7, U2.18, U2.21, U2.25, U2.26, U3.5, U3.6, U3.7, U3.8, U3.9, U4.3, U4.5, U5.4, U5.9, U6.5, U6.6, U6.7, U6.8, U6.9, U7.1, U8.2, U9.2, U10.2, U11.4, U12.2, U13.6, U13.9, U14.2, U15.2, U17.C, U18.2, U18.3, U19.1, U19.3
INPUT_USBPOWER_5V: C25.1, R6.1, R29.2, U3.1, U13.1, U13.2
NET_U1_7: R4.1, U1.7, U19.4
NET_U1_60: R5.1, U1.60
NET_U1_62: U16.3, U16.4
NET_U2_14: R7.1, U2.14
NET_U2_17: C13.1, U2.17
NET_U2_19: R8.1, U2.19
NET_U3_2: U2.16, U3.2
NET_U3_3: U2.15, U3.3
NET_U4_9: R13.1, U4.9
NET_U11_3: R18.1, U11.3
NET_U11_5: R17.1, U11.5
NET_U11_7: R19.2, R20.1, U11.7
NET_U12_3: I1.1, U12.3
NET_U12_5: R21.1, R22.1, U12.5
NET_U12_ATNET_3: I1.2, R22.2
NET_U13_5: R29.1, U13.5
NET_U13_8: R28.1, U13.8
NET_U15_1: R24.1, R25.1, U15.1
NET_U15_3: R26.2, R27.1, U15.3
NET_U15_4: R23.1, U15.4, U18.4, U19.2
NET_U16_1: R2.1, U16.1, U16.2
PROC_LPUART1_CTS: U1.34, U2.3
PROC_LPUART1_RTS: U1.33, U2.11
PROC_LPUART1_RX: U1.8, U2.1
PROC_LPUART1_TX: U1.9, U2.5
PROC_QUADSPI_BK1_IO0: U1.27, U5.5
PROC_QUADSPI_BK1_IO1: U1.26, U5.2
PROC_QUADSPI_BK1_IO2: R15.1, U1.23, U5.3
PROC_QUADSPI_BK1_IO3: R16.1, U1.22, U5.7
PROC_QUADSPI_CLK: U1.29, U5.6
PROC_QUADSPI_NCS: R14.1, U1.30, U5.1
PROC_SYS_JTCK_SWCLK: R12.1, U1.49, U4.4
PROC_SYS_JTDI: R10.1, U1.50, U4.8
PROC_SYS_JTDO_SWO: U1.55, U4.6
PROC_SYS_JTMS_SWDIO: R11.1, U1.46, U4.2
PROC_USB_OTG_FS_DM: U1.44, U6.2, U7.3
PROC_USB_OTG_FS_DP: U1.45, U6.3, U7.2
PROC_USB_OTG_FS_VBUS: U1.42, U6.1, U7.4
RST_OUT_U4_JTAG_RST_B: R9.1, U4.10, U18.1
VCC_S1_3V7: C20.1, C22.1, C26.1, R18.2, U11.8, U12.4, U13.3, U13.4, U14.1
VCC_TIER1_1V8: C1.1, C2.1, C3.1, C4.1, C5.1, C6.1, C7.1, C9.1, C10.1, C14.1, C15.1, C16.1, C21.1, C24.1, C27.1, C28.1, R4.2, R9.2, R10.2, R11.2, R14.2, R15.2, R16.2, R17.2, R19.1, R23.2, R24.2, R26.1, U1.1, U1.13, U1.19, U1.32, U1.64, U2.4, U4.1, U5.8, U11.1, U15.6, U18.5, U19.5
VCC_TIER1_3V3: C8.1, C11.1, C12.1, C17.1, C18.1, C19.1, C23.2, I1.2, R7.2, R22.2, U1.48, U2.20, U8.4, U9.4, U10.4
